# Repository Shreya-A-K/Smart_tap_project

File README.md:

# Smart_tap_project
This repository contains the schematic diagram for a smart tap based on IR sensor.
This a simple project made using components like IR sensor, 555 timer IC, n-MOSFET, solenoid valve, DC motor etc.

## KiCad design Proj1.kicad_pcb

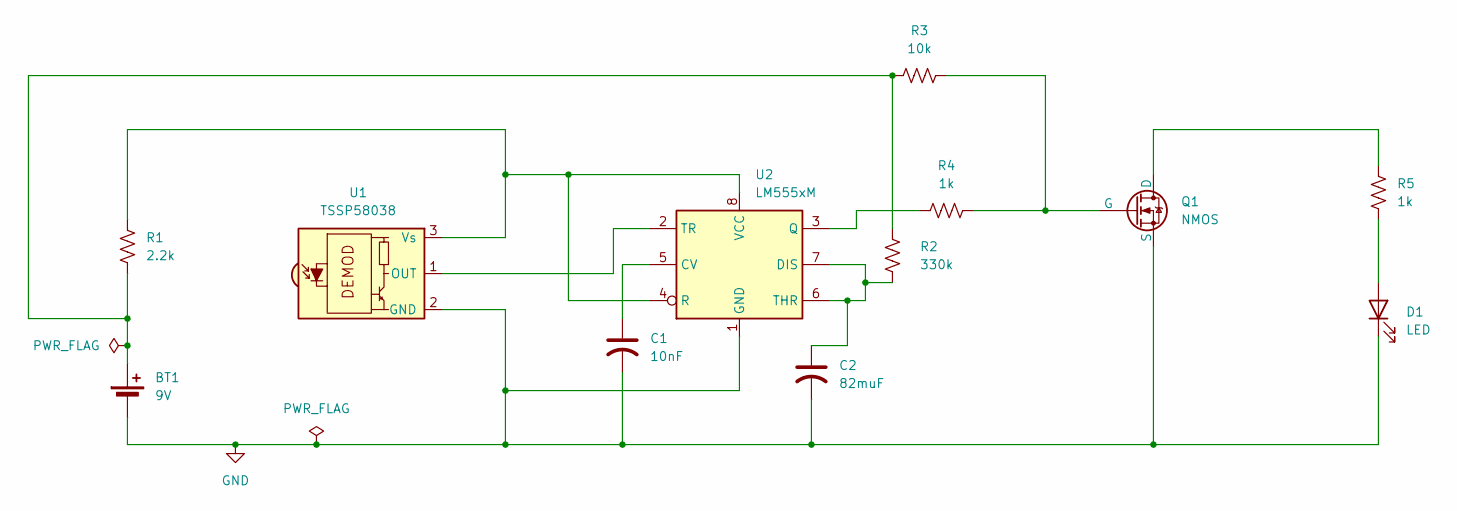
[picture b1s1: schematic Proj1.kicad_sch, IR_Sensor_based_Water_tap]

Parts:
BT1: 9V; BatteryHolder_Keystone_103_1x20mm
C1: 10nF; C_0603_1608Metric
C2: 82muF; C_0603_1608Metric
D1: LED; LED_0201_0603Metric
Q1: NMOS; Mosfet
R1: 2.2k; R_0201_0603Metric
R2: 330k; R_0201_0603Metric
R3: 10k; R_0201_0603Metric
R4, R5: 1k; R_0201_0603Metric
U1: TSSP58038; Vishay_MINICAST-3Pin
U2: LM555xM; SOIC-8_3.9x4.9mm_P1.27mm

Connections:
GND: BT1.2 (-), C1.2, C2.2, D1.1 (K), Q1.3 (S), U1.2 (GND), U2.1 (GND)
unnamed: BT1.1 (+), R1.2, R2.1, R3.1
unnamed: D1.2 (A), R5.2
unnamed: Q1.1 (D), R5.1
unnamed: Q1.2 (G), R3.2, R4.2
unnamed: U1.1 (OUT), U2.2 (TR)
unnamed: R1.1, U1.3 (Vs), U2.4 (R), U2.8 (VCC)
unnamed: C1.1, U2.5 (CV)
unnamed: C2.1, R2.2, U2.6 (THR), U2.7 (DIS)
unnamed: R4.1, U2.3 (Q)

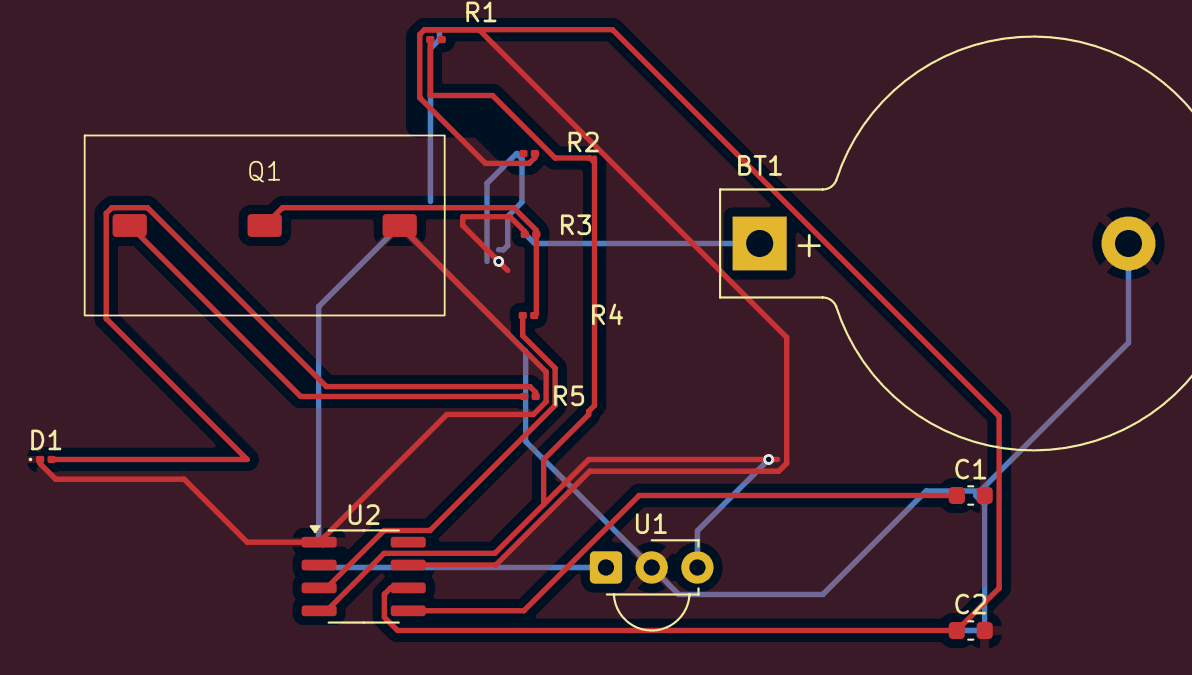
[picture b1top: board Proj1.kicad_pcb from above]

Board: 2 copper layers, 12 parts (0 on the bottom side), 10 nets.
